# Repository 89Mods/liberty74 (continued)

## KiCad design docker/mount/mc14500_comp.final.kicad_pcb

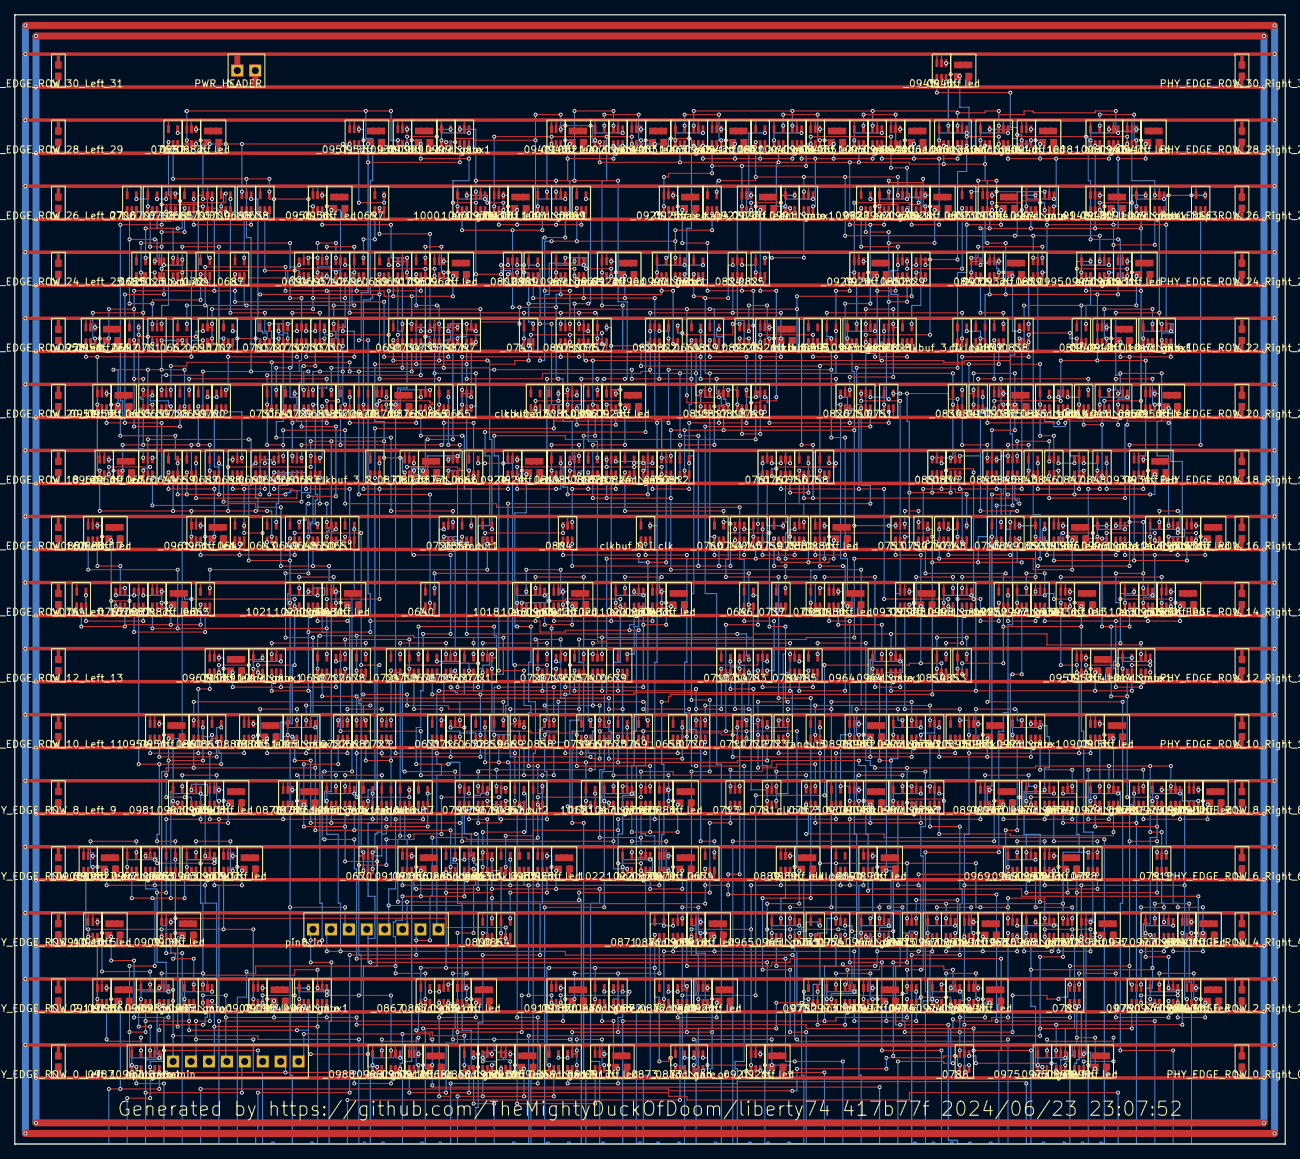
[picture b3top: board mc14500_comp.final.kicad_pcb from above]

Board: 2 copper layers, 180.0 x 160.0 mm, 592 parts (0 on the bottom side), 481 nets.

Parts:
PHY_EDGE_ROW_0_Left_1, PHY_EDGE_ROW_0_Right_0, PHY_EDGE_ROW_2_Left_3, PHY_EDGE_ROW_2_Right_2, PHY_EDGE_ROW_4_Left_5, PHY_EDGE_ROW_4_Right_4, PHY_EDGE_ROW_6_Left_7, PHY_EDGE_ROW_6_Right_6, PHY_EDGE_ROW_8_Left_9, PHY_EDGE_ROW_8_Right_8, PHY_EDGE_ROW_10_Left_11, PHY_EDGE_ROW_10_Right_10, PHY_EDGE_ROW_12_Left_13, PHY_EDGE_ROW_12_Right_12, PHY_EDGE_ROW_14_Left_15, PHY_EDGE_ROW_14_Right_14, PHY_EDGE_ROW_16_Left_17, PHY_EDGE_ROW_16_Right_16, PHY_EDGE_ROW_18_Left_19, PHY_EDGE_ROW_18_Right_18, PHY_EDGE_ROW_20_Left_21, PHY_EDGE_ROW_20_Right_20, PHY_EDGE_ROW_22_Left_23, PHY_EDGE_ROW_22_Right_22, PHY_EDGE_ROW_24_Left_25, PHY_EDGE_ROW_24_Right_24, PHY_EDGE_ROW_26_Left_27, PHY_EDGE_ROW_26_Right_26, PHY_EDGE_ROW_28_Left_29, PHY_EDGE_ROW_28_Right_28, PHY_EDGE_ROW_30_Left_31, PHY_EDGE_ROW_30_Right_30: PWR_CAP; PWR_CAP_N
PWR_HEADER: PWR_HEADER; PWR_HEADER_N
_0635_, _0636_, _0660_, _0711_, _0742_: OR3_74LVC1G332; OR3_74LVC1G332_N
_0638_, _0640_, _0641_, _0642_, _0658_, _0662_, _0671_, _0676_, _0685_, _0692_, _0706_, _0737_, _0764_, _0765_, _0769_, _0801_, _0828_: INV_74LVC1G04; INV_74LVC1G04_N
_0639_, _0683_, _0688_, _0701_, _0712_, _0715_, _0717_, _0719_, _0722_, _0727_, _0729_, _0755_, _0761_, _0774_, _0775_, _0776_, _0777_, _0778_, _0779_, _0780_, _0786_, _0788_, _0789_, _0790_, _0791_, _0792_, _0793_, _0802_, _0829_, _0839_, _0860_, _0863_, _0876__mux, _0877__mux, _0964__mux1, _0965__mux1, _0966__mux1, _0967__mux1, _0968__mux1, _0969__mux1, _0970__mux1, _0971__mux1, _0972__mux1, _0973__mux1, _0974__mux1, _0975__mux1, _0976__mux1, _0977__mux1, _0978__mux1, _0979__mux1, _0980__mux1, _0981__mux1, _0982__mux1, _0983__mux1, _0984__mux1, _0985__mux1, _0986__mux1, _0987__mux1, _0988__mux1, _0989__mux1, _0990__mux1, _0991__mux1, _0992__mux1, _0993__mux1, _0994__mux1, _0995__mux1, _0996__mux1, _0997__mux1, _0998__mux1, _0999__mux1, _1000__mux1, _1001__mux1, _1002__mux1, _1003__mux1, _1004__mux1, _1005__mux1, _1006__mux1, _1007__mux1, _1008__mux1, _1009__mux1, _1010__mux1, _1011__mux1, _1012__mux1, _1013__mux1, _1014__mux1, _1015__mux1, _1016__mux1, _1017__mux1, _1018__mux1, _1019__mux1, _1020__mux1, _1021__mux1, _1022__mux1, _1023__mux1, _1023__mux2: MUX2_74LVC1G157; MUX2_74LVC1G157_N
_0643_, _0659_, _0687_, _0699_, _0704_, _0709_, _0710_, _0718_, _0720_, _0756_, _0758_, _0806_, _0809_, _0861_, _0864_: OR2_74LVC1G32; OR2_74LVC1G32_N
_0644_, _0648_, _0649_, _0682_, _0686_, _0690_, _0702_, _0703_, _0728_, _0731_, _0745_, _0757_, _0760_, _0822_, _0837_: NAND2_74LVC1G00; NAND2_74LVC1G00_N
_0645_, _0667_, _0669_, _0693_, _0700_, _0705_, _0713_, _0726_, _0730_, _0735_, _0740_, _0747_, _0749_, _0750_, _0752_, _0753_, _0754_, _0762_, _0784_, _0794_, _0797_, _0799_, _0803_, _0804_, _0810_, _0815_, _0817_, _0824_, _0826_, _0832_, _0836_, _0840_, _0849_, _0851_, _0858_: AND3_74LVC1G11; AND3_74LVC1G11_N
_0646_, _0651_, _0664_, _0672_, _0673_, _0675_, _0677_, _0678_, _0679_, _0680_, _0681_, _0697_, _0707_, _0724_, _0736_, _0738_, _0743_, _0746_, _0748_, _0751_, _0759_, _0763_, _0771_, _0782_, _0785_, _0814_, _0834_, _0843_, _0844_, _0848_, _0853_, _0856_, _0859_, _0862_, _0866__and_gate, _0867__and_gate, _0868__and_gate, _0869__and_gate, _0870__and_gate, _0871__and_gate, _0872__and_gate, _0873__and_gate, _0874__and_gate, _0875__and_gate, _0964__and_gate, _0965__and_gate, _0966__and_gate, _0967__and_gate, _0968__and_gate, _0969__and_gate, _0970__and_gate, _0971__and_gate, _0972__and_gate, _0973__and_gate, _0974__and_gate, _0975__and_gate, _0976__and_gate, _0977__and_gate, _0978__and_gate, _0979__and_gate, _0980__and_gate, _0981__and_gate, _0982__and_gate, _0983__and_gate, _0984__and_gate, _0985__and_gate, _0986__and_gate, _0987__and_gate, _0988__and_gate, _0989__and_gate, _0990__and_gate, _0991__and_gate, _0992__and_gate, _0993__and_gate, _0994__and_gate, _0995__and_gate, _0996__and_gate, _0997__and_gate, _0998__and_gate, _0999__and_gate, _1000__and_gate, _1001__and_gate, _1002__and_gate, _1003__and_gate, _1004__and_gate, _1005__and_gate, _1006__and_gate, _1007__and_gate, _1008__and_gate, _1009__and_gate, _1010__and_gate, _1011__and_gate, _1012__and_gate, _1013__and_gate, _1014__and_gate, _1015__and_gate, _1016__and_gate, _1017__and_gate, _1018__and_gate, _1019__and_gate, _1020__and_gate, _1021__and_gate, _1022__and_gate: AND2_74LVC1G08; AND2_74LVC1G08_N
_0650_, _0694_, _0695_, _0708_, _0823_, _0845_: NOR3_74LVC1G27; NOR3_74LVC1G27_N
_0661_, _0691_, _0698_, _0714_, _0732_, _0733_, _0734_, _0744_, _0766_, _0767_, _0773_, _0783_, _0811_, _0813_, _0821_, _0830_, _0838_, _0841_, _0846_, _0847_, _0866__and_or, _0867__and_or, _0868__and_or, _0869__and_or, _0870__and_or, _0871__and_or, _0872__and_or, _0873__and_or, _0874__and_or, _0875__and_or: AO21_74LVC1G0832; AO21_74LVC1G0832_N
_0663_, _0666_, _0674_, _0684_, _0689_, _0739_, _0800_, _0812_, _0819_, _0820_, _0857_, _0865_: NOR2_74LVC1G02; NOR2_74LVC1G02_N
_0665_, _0668_, _0670_, _0716_, _0721_, _0723_, _0725_, _0770_, _0772_, _0781_, _0796_, _0798_, _0807_, _0842_: NAND3_74LVC1G10; NAND3_74LVC1G10_N
_0696_, _0805_, _0816_, _0818_, _0825_, _0827_, _0833_, _0835_, _0850_, _0852_, _0854_: XOR2_74LVC1G86; XOR2_74LVC1G86_N
_0876__dff, _0877__dff, _0878__dff, _0879__dff, _0880__dff, _0881__dff, _0882__dff, _0883__dff, _0884__dff, _0885__dff, _0886__dff, _0887__dff, _0888__dff, _0889__dff, _0890__dff, _0891__dff, _0892__dff, _0893__dff, _0894__dff, _0895__dff, _0896__dff, _0897__dff, _0898__dff, _0899__dff, _0900__dff, _0901__dff, _0902__dff, _0903__dff, _0904__dff, _0905__dff, _0906__dff, _0907__dff, _0908__dff, _0909__dff, _0910__dff, _0911__dff, _0912__dff, _0913__dff, _0914__dff, _0915__dff, _0916__dff, _0917__dff, _0918__dff, _0919__dff, _0920__dff, _0921__dff, _0922__dff, _0923__dff, _0924__dff, _0925__dff, _0926__dff, _0927__dff, _0928__dff, _0929__dff, _0930__dff, _0931__dff, _0932__dff, _0933__dff, _0934__dff, _0935__dff, _0936__dff, _0937__dff, _0938__dff, _0939__dff, _0940__dff, _0941__dff, _0942__dff, _0943__dff, _0944__dff, _0945__dff, _0946__dff, _0947__dff, _0948__dff, _0949__dff, _0950__dff, _0951__dff, _0952__dff, _0953__dff, _0954__dff, _0955__dff, _0956__dff, _0957__dff, _0958__dff, _0959__dff, _0960__dff, _0961__dff, _0962__dff, _0963__dff: DFF_74LVC1G175; DFF_74LVC1G175_N
_0876__led, _0877__led, _0878__led, _0879__led, _0880__led, _0881__led, _0882__led, _0883__led, _0884__led, _0885__led, _0886__led, _0887__led, _0888__led, _0889__led, _0890__led, _0891__led, _0892__led, _0893__led, _0894__led, _0895__led, _0896__led, _0897__led, _0898__led, _0899__led, _0900__led, _0901__led, _0902__led, _0903__led, _0904__led, _0905__led, _0906__led, _0907__led, _0908__led, _0909__led, _0910__led, _0911__led, _0912__led, _0913__led, _0914__led, _0915__led, _0916__led, _0917__led, _0918__led, _0919__led, _0920__led, _0921__led, _0922__led, _0923__led, _0924__led, _0925__led, _0926__led, _0927__led, _0928__led, _0929__led, _0930__led, _0931__led, _0932__led, _0933__led, _0934__led, _0935__led, _0936__led, _0937__led, _0938__led, _0939__led, _0940__led, _0941__led, _0942__led, _0943__led, _0944__led, _0945__led, _0946__led, _0947__led, _0948__led, _0949__led, _0950__led, _0951__led, _0952__led, _0953__led, _0954__led, _0955__led, _0956__led, _0957__led, _0958__led, _0959__led, _0960__led, _0961__led, _0962__led, _0963__led: Led_Res_0603; Led_Res_0603_N
clkbuf_0_i_clk, clkbuf_3_0__f_i_clk, clkbuf_3_1__f_i_clk, clkbuf_3_2__f_i_clk, clkbuf_3_3__f_i_clk, clkbuf_3_4__f_i_clk, clkbuf_3_5__f_i_clk, clkbuf_3_6__f_i_clk, clkbuf_3_7__f_i_clk: BUF_74LVC1G125; BUF_74LVC1G125_N
clkload0, clkload1, clkload2, clkload3, clkload4, clkload5, clkload6: BUF_74LVC1G125; BUF_74LVC1G125_N
fanout1, fanout2, fanout5, fanout6, fanout7: BUF_74LVC1G125; BUF_74LVC1G125_N
max_cap3, max_cap4: BUF_74LVC1G125; BUF_74LVC1G125_N
pin8_io, pin8_sramin: PININ_8; PININ_8_N

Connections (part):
DATA_OUT: _0860_.1 (I1), _0863_.1 (I1), _0866__and_gate.2 (A), _0957__dff.4 (Q), _0957__led.1 (I), _0981__mux1.1 (I1), _0999__mux1.1 (I1), _1015__mux1.3 (I0), _1016__mux1.3 (I0), _1017__mux1.1 (I1), _1018__mux1.1 (I1), _1019__mux1.1 (I1), _1020__mux1.1 (I1), _1021__mux1.1 (I1), _1022__mux1.1 (I1)
FLAG_O: _0646_.4 (Y), _0772_.1 (A)
GND: PHY_EDGE_ROW_0_Left_1.1 (GND), PHY_EDGE_ROW_0_Right_0.1 (GND), PHY_EDGE_ROW_2_Left_3.1 (GND), PHY_EDGE_ROW_2_Right_2.1 (GND), PHY_EDGE_ROW_4_Left_5.1 (GND), PHY_EDGE_ROW_4_Right_4.1 (GND), PHY_EDGE_ROW_6_Left_7.1 (GND), PHY_EDGE_ROW_6_Right_6.1 (GND), PHY_EDGE_ROW_8_Left_9.1 (GND), PHY_EDGE_ROW_8_Right_8.1 (GND), PHY_EDGE_ROW_10_Left_11.1 (GND), PHY_EDGE_ROW_10_Right_10.1 (GND), PHY_EDGE_ROW_12_Left_13.1 (GND), PHY_EDGE_ROW_12_Right_12.1 (GND), PHY_EDGE_ROW_14_Left_15.1 (GND), PHY_EDGE_ROW_14_Right_14.1 (GND), PHY_EDGE_ROW_16_Left_17.1 (GND), PHY_EDGE_ROW_16_Right_16.1 (GND), PHY_EDGE_ROW_18_Left_19.1 (GND), PHY_EDGE_ROW_18_Right_18.1 (GND), PHY_EDGE_ROW_20_Left_21.1 (GND), PHY_EDGE_ROW_20_Right_20.1 (GND), PHY_EDGE_ROW_22_Left_23.1 (GND), PHY_EDGE_ROW_22_Right_22.1 (GND), PHY_EDGE_ROW_24_Left_25.1 (GND), PHY_EDGE_ROW_24_Right_24.1 (GND), PHY_EDGE_ROW_26_Left_27.1 (GND), PHY_EDGE_ROW_26_Right_26.1 (GND), PHY_EDGE_ROW_28_Left_29.1 (GND), PHY_EDGE_ROW_28_Right_28.1 (GND), PHY_EDGE_ROW_30_Left_31.1 (GND), PHY_EDGE_ROW_30_Right_30.1 (GND), PWR_HEADER.2 (GND), _0635_.2 (GND), _0636_.2 (GND), _0638_.1 (GND), _0638_.3 (GND), _0639_.2 (GND), _0640_.1 (GND), _0640_.3 (GND), _0641_.1 (GND), _0641_.3 (GND), _0642_.1 (GND), _0642_.3 (GND), _0643_.3 (GND), _0644_.3 (GND), _0645_.2 (GND), _0646_.3 (GND), _0648_.3 (GND), _0649_.3 (GND), _0650_.2 (GND), _0651_.3 (GND), _0658_.1 (GND), _0658_.3 (GND), _0659_.3 (GND), _0660_.2 (GND), _0661_.2 (GND), _0662_.1 (GND), _0662_.3 (GND), _0663_.3 (GND), _0664_.3 (GND), _0665_.2 (GND), _0666_.3 (GND), _0667_.2 (GND), _0668_.2 (GND), _0669_.2 (GND), _0670_.2 (GND), _0671_.1 (GND), _0671_.3 (GND), _0672_.3 (GND), _0673_.3 (GND), _0674_.3 (GND), _0675_.3 (GND), _0676_.1 (GND), _0676_.3 (GND), _0677_.3 (GND), _0678_.3 (GND), _0679_.3 (GND), _0680_.3 (GND), _0681_.3 (GND), _0682_.3 (GND), _0683_.2 (GND), _0684_.3 (GND), _0685_.1 (GND), _0685_.3 (GND), _0686_.3 (GND)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
PC[0]: _0752_.6 (C), _0801_.2 (A), _0804_.1 (A), _0922__dff.4 (Q), _0922__led.1 (I), _0989__mux1.3 (I0)
PC[1]: _0752_.3 (B), _0805_.2 (A), _0811_.1 (A), _0923__dff.4 (Q), _0923__led.1 (I)
PC[2]: _0752_.1 (A), _0811_.6 (C), _0874__and_gate.2 (A), _0924__dff.4 (Q), _0924__led.1 (I)
PC[3]: _0749_.6 (C), _0816_.2 (A), _0817_.1 (A), _0824_.3 (B), _0925__dff.4 (Q), _0925__led.1 (I)
PC[4]: _0749_.3 (B), _0818_.2 (A), _0821_.6 (C), _0824_.1 (A), _0926__dff.4 (Q), _0926__led.1 (I)
PC[5]: _0749_.1 (A), _0825_.2 (A), _0927__dff.4 (Q), _0927__led.1 (I)
PC[6]: _0750_.6 (C), _0827_.2 (A), _0830_.1 (A), _0832_.3 (B), _0928__dff.4 (Q), _0928__led.1 (I)
PC[7]: _0750_.3 (B), _0828_.2 (A), _0832_.1 (A), _0929__dff.4 (Q), _0929__led.1 (I), _0993__mux1.3 (I0)
PC[8]: _0750_.1 (A), _0833_.2 (A), _0930__dff.4 (Q), _0930__led.1 (I)
PC[9]: _0746_.1 (B), _0835_.2 (A), _0838_.1 (A), _0931__dff.4 (Q), _0931__led.1 (I)
PC[10]: _0746_.2 (A), _0838_.6 (C), _0932__dff.4 (Q), _0932__led.1 (I)
PC[11]: _0747_.6 (C), _0841_.6 (C), _0842_.1 (A), _0849_.3 (B), _0933__dff.4 (Q), _0933__led.1 (I)
PC[12]: _0747_.3 (B), _0845_.1 (A), _0847_.1 (A), _0849_.1 (A), _0934__dff.4 (Q), _0934__led.1 (I)
PC[13]: _0747_.1 (A), _0850_.2 (A), _0935__dff.4 (Q), _0935__led.1 (I)
PC[14]: _0754_.1 (A), _0852_.2 (A), _0853_.2 (A), _0936__dff.4 (Q), _0936__led.1 (I)
PC[15]: _0753_.1 (A), _0854_.2 (A), _0937__dff.4 (Q), _0937__led.1 (I)
PC[16]: _0745_.2 (A), _0755_.3 (I0), _0759_.2 (A), _0881__dff.4 (Q), _0881__led.1 (I)
RR: _0689_.2 (A), _0696_.2 (A), _0701_.6 (S), _0704_.1 (B), _0706_.2 (A), _0730_.1 (A), _0734_.6 (C), _0962__dff.4 (Q), _0962__led.1 (I), _1023__mux1.6 (S)
SCLK: _0715_.1 (I1), _0879__dff.4 (Q), _0879__led.1 (I), _1022__mux1.3 (I0)
SDO: _0722_.1 (I1), _0878__dff.4 (Q), _0878__led.1 (I), _1016__mux1.1 (I1)
VDD: PHY_EDGE_ROW_0_Left_1.2 (VDD), PHY_EDGE_ROW_0_Right_0.2 (VDD), PHY_EDGE_ROW_2_Left_3.2 (VDD), PHY_EDGE_ROW_2_Right_2.2 (VDD), PHY_EDGE_ROW_4_Left_5.2 (VDD), PHY_EDGE_ROW_4_Right_4.2 (VDD), PHY_EDGE_ROW_6_Left_7.2 (VDD), PHY_EDGE_ROW_6_Right_6.2 (VDD), PHY_EDGE_ROW_8_Left_9.2 (VDD), PHY_EDGE_ROW_8_Right_8.2 (VDD), PHY_EDGE_ROW_10_Left_11.2 (VDD), PHY_EDGE_ROW_10_Right_10.2 (VDD), PHY_EDGE_ROW_12_Left_13.2 (VDD), PHY_EDGE_ROW_12_Right_12.2 (VDD), PHY_EDGE_ROW_14_Left_15.2 (VDD), PHY_EDGE_ROW_14_Right_14.2 (VDD), PHY_EDGE_ROW_16_Left_17.2 (VDD), PHY_EDGE_ROW_16_Right_16.2 (VDD), PHY_EDGE_ROW_18_Left_19.2 (VDD), PHY_EDGE_ROW_18_Right_18.2 (VDD), PHY_EDGE_ROW_20_Left_21.2 (VDD), PHY_EDGE_ROW_20_Right_20.2 (VDD), PHY_EDGE_ROW_22_Left_23.2 (VDD), PHY_EDGE_ROW_22_Right_22.2 (VDD), PHY_EDGE_ROW_24_Left_25.2 (VDD), PHY_EDGE_ROW_24_Right_24.2 (VDD), PHY_EDGE_ROW_26_Left_27.2 (VDD), PHY_EDGE_ROW_26_Right_26.2 (VDD), PHY_EDGE_ROW_28_Left_29.2 (VDD), PHY_EDGE_ROW_28_Right_28.2 (VDD), PHY_EDGE_ROW_30_Left_31.2 (VDD), PHY_EDGE_ROW_30_Right_30.2 (VDD), PWR_HEADER.1 (VDD), _0635_.5 (VDD), _0636_.5 (VDD), _0638_.6 (VDD), _0639_.5 (VDD), _0640_.6 (VDD), _0641_.6 (VDD), _0642_.6 (VDD), _0643_.6 (VDD), _0644_.6 (VDD), _0645_.5 (VDD), _0646_.6 (VDD), _0648_.6 (VDD), _0649_.6 (VDD), _0650_.5 (VDD), _0651_.6 (VDD), _0658_.6 (VDD), _0659_.6 (VDD), _0660_.5 (VDD), _0661_.5 (VDD), _0662_.6 (VDD), _0663_.6 (VDD), _0664_.6 (VDD), _0665_.5 (VDD), _0666_.6 (VDD), _0667_.5 (VDD), _0668_.5 (VDD), _0669_.5 (VDD), _0670_.5 (VDD), _0671_.6 (VDD), _0672_.6 (VDD), _0673_.6 (VDD), _0674_.6 (VDD), _0675_.6 (VDD), _0676_.6 (VDD), _0677_.6 (VDD), _0678_.6 (VDD), _0679_.6 (VDD), _0680_.6 (VDD), _0681_.6 (VDD), _0682_.6 (VDD), _0683_.5 (VDD), _0684_.6 (VDD), _0685_.6 (VDD), _0686_.6 (VDD), _0687_.6 (VDD), _0688_.5 (VDD), _0689_.6 (VDD), _0690_.6 (VDD), _0691_.5 (VDD), _0692_.6 (VDD), _0693_.5 (VDD), _0694_.5 (VDD), _0695_.5 (VDD)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
X1: _0638_.2 (A), _0643_.2 (A), _0644_.2 (A), _0650_.1 (A), _0660_.1 (A), _0664_.2 (A), _0683_.6 (S), _0688_.6 (S), _0693_.1 (A), _0694_.1 (A), _0698_.6 (C), _0705_.1 (A), _0708_.1 (A), _0744_.1 (A), _0760_.2 (A), _0797_.1 (A), _0804_.3 (B), _0815_.1 (A), _0821_.1 (A), _0876__dff.1 (CLK), _0877__dff.1 (CLK), _0882__dff.4 (Q), _0882__led.1 (I), _0957__dff.1 (CLK), _0958__dff.1 (CLK), _0959__dff.1 (CLK), _0960__dff.1 (CLK), _0961__dff.1 (CLK), _0962__dff.1 (CLK), _1023__mux2.6 (S)
_0000_: _0736_.4 (Y), _0962__dff.3 (D)
_0001_: _0697_.4 (Y), _0957__dff.3 (D)
_0002_: _0691_.4 (Y), _0956__dff.3 (D)
_0003_: _0883__dff.3 (D), _1020__and_gate.4 (Y)
_0004_: _0884__dff.3 (D), _1021__and_gate.4 (Y)
_0005_: _0885__dff.3 (D), _1017__and_gate.4 (Y)
_0006_: _0886__dff.3 (D), _1015__and_gate.4 (Y)
_0007_: _0913__dff.3 (D), _1018__and_gate.4 (Y)
_0008_: _0963__dff.3 (D), _1019__and_gate.4 (Y)
_0009_: _0879__dff.3 (D), _1022__and_gate.4 (Y)
_0010_: _0878__dff.3 (D), _1016__and_gate.4 (Y)
_0011_: _0638_.4 (Y), _0639_.6 (S), _0699_.2 (A), _0729_.6 (S), _0763_.2 (A), _0956__dff.1 (CLK)
_0012_: _0880__dff.3 (D), _0964__and_gate.4 (Y)
_0013_: _0762_.4 (Y), _0881__dff.3 (D)
_0014_: _0763_.4 (Y), _0882__dff.3 (D)
_0015_: _0766_.4 (Y), _0887__dff.3 (D)
_0016_: _0767_.4 (Y), _0888__dff.3 (D)
_0017_: _0889__dff.3 (D), _0965__and_gate.4 (Y)
_0018_: _0890__dff.3 (D), _0966__and_gate.4 (Y)
_0019_: _0891__dff.3 (D), _0967__and_gate.4 (Y)
_0020_: _0892__dff.3 (D), _0968__and_gate.4 (Y)
_0021_: _0893__dff.3 (D), _0969__and_gate.4 (Y)
_0022_: _0894__dff.3 (D), _0970__and_gate.4 (Y)
_0023_: _0895__dff.3 (D), _0971__and_gate.4 (Y)
_0024_: _0896__dff.3 (D), _0972__and_gate.4 (Y)
_0025_: _0897__dff.3 (D), _0973__and_gate.4 (Y)
_0026_: _0898__dff.3 (D), _0974__and_gate.4 (Y)
_0027_: _0899__dff.3 (D), _0975__and_gate.4 (Y)
_0028_: _0900__dff.3 (D), _0976__and_gate.4 (Y)
_0029_: _0901__dff.3 (D), _0977__and_gate.4 (Y)
_0030_: _0902__dff.3 (D), _0978__and_gate.4 (Y)
_0031_: _0903__dff.3 (D), _0979__and_gate.4 (Y)
_0032_: _0904__dff.3 (D), _0980__and_gate.4 (Y)
_0033_: _0905__dff.3 (D), _0981__and_gate.4 (Y)
_0034_: _0906__dff.3 (D), _0982__and_gate.4 (Y)
_0035_: _0907__dff.3 (D), _0983__and_gate.4 (Y)
_0036_: _0908__dff.3 (D), _0984__and_gate.4 (Y)
_0037_: _0909__dff.3 (D), _0985__and_gate.4 (Y)
_0038_: _0910__dff.3 (D), _0986__and_gate.4 (Y)
_0039_: _0911__dff.3 (D), _0987__and_gate.4 (Y)
_0040_: _0912__dff.3 (D), _0988__and_gate.4 (Y)
_0041_: _0866__and_or.4 (Y), _0914__dff.3 (D)
_0042_: _0867__and_or.4 (Y), _0915__dff.3 (D)
_0043_: _0868__and_or.4 (Y), _0916__dff.3 (D)
_0044_: _0869__and_or.4 (Y), _0917__dff.3 (D)
_0045_: _0870__and_or.4 (Y), _0918__dff.3 (D)
_0046_: _0871__and_or.4 (Y), _0919__dff.3 (D)
_0047_: _0872__and_or.4 (Y), _0920__dff.3 (D)
_0048_: _0873__and_or.4 (Y), _0921__dff.3 (D)
_0049_: _0922__dff.3 (D), _0989__and_gate.4 (Y)
_0050_: _0810_.4 (Y), _0923__dff.3 (D)
_0051_: _0814_.4 (Y), _0924__dff.3 (D)
_0052_: _0925__dff.3 (D), _0990__and_gate.4 (Y)
_0053_: _0823_.4 (Y), _0926__dff.3 (D)
_0054_: _0927__dff.3 (D), _0991__and_gate.4 (Y)
_0055_: _0928__dff.3 (D), _0992__and_gate.4 (Y)
_0056_: _0929__dff.3 (D), _0993__and_gate.4 (Y)
_0057_: _0930__dff.3 (D), _0994__and_gate.4 (Y)
_0058_: _0931__dff.3 (D), _0995__and_gate.4 (Y)
_0059_: _0840_.4 (Y), _0932__dff.3 (D)
_0060_: _0844_.4 (Y), _0933__dff.3 (D)
_0061_: _0848_.4 (Y), _0934__dff.3 (D)
_0062_: _0935__dff.3 (D), _0996__and_gate.4 (Y)
_0063_: _0936__dff.3 (D), _0997__and_gate.4 (Y)
_0064_: _0937__dff.3 (D), _0998__and_gate.4 (Y)
_0065_: _0938__dff.3 (D), _0999__and_gate.4 (Y)
_0066_: _0939__dff.3 (D), _1000__and_gate.4 (Y)
_0067_: _0940__dff.3 (D), _1001__and_gate.4 (Y)
_0068_: _0941__dff.3 (D), _1002__and_gate.4 (Y)
_0069_: _0942__dff.3 (D), _1003__and_gate.4 (Y)
_0070_: _0943__dff.3 (D), _1004__and_gate.4 (Y)
_0071_: _0944__dff.3 (D), _1005__and_gate.4 (Y)
_0072_: _0945__dff.3 (D), _1006__and_gate.4 (Y)
_0073_: _0946__dff.3 (D), _1007__and_gate.4 (Y)
_0074_: _0947__dff.3 (D), _1008__and_gate.4 (Y)
_0075_: _0948__dff.3 (D), _1009__and_gate.4 (Y)
_0076_: _0949__dff.3 (D), _1010__and_gate.4 (Y)
_0077_: _0950__dff.3 (D), _1011__and_gate.4 (Y)
_0078_: _0951__dff.3 (D), _1012__and_gate.4 (Y)
_0079_: _0952__dff.3 (D), _1013__and_gate.4 (Y)
_0080_: _0953__dff.3 (D), _1014__and_gate.4 (Y)
_0082_: _0861_.4 (Y), _0954__dff.3 (D)
_0083_: _0864_.4 (Y), _0955__dff.3 (D)
_0085_: _0635_.4 (Y), _0639_.3 (I0)
_0086_: _0636_.4 (Y), _0639_.1 (I1)
_0088_: _0639_.4 (Y), _0640_.2 (A), _0731_.2 (A), _0734_.1 (A)
_0089_: _0640_.4 (Y), _0646_.2 (A), _0783_.1 (A)
_0090_: _0641_.4 (Y), _0645_.1 (A), _0651_.2 (A), _0733_.1 (A)
_0091_: _0642_.4 (Y), _0643_.1 (B), _0660_.3 (B), _0698_.1 (A)
_0092_: _0643_.4 (Y), _0645_.3 (B)
_0093_: _0644_.4 (Y), _0645_.6 (C), _0659_.1 (B), _0700_.1 (A)
_0094_: _0645_.4 (Y), _0646_.1 (B), _0731_.1 (B), _0734_.3 (B), _0783_.3 (B)
_0096_: _0648_.4 (Y), _0650_.3 (B), _0729_.1 (I1)
_0097_: _0649_.4 (Y), _0650_.6 (C), _0683_.3 (I0)
_0098_: _0650_.4 (Y), _0651_.1 (B)
_0105_: _0658_.4 (Y), _0667_.3 (B), _0711_.6 (C)
_0106_: _0659_.4 (Y), _0661_.1 (A)
_0107_: _0660_.4 (Y), _0661_.3 (B)
_0108_: _0661_.4 (Y), _0666_.2 (A), _0857_.1 (B), _0865_.2 (A)
_0109_: _0662_.4 (Y), _0665_.1 (A), _0687_.2 (A), _0693_.3 (B), _0704_.2 (A), _0797_.3 (B)
_0110_: _0663_.4 (Y), _0804_.6 (C), fanout1.2 (A)
_0111_: _0664_.4 (Y), _0665_.6 (C), _0784_.3 (B), _0803_.1 (A), _0807_.1 (A), _0817_.3 (B), _0826_.1 (A), _0989__mux1.6 (S)
_0112_: _0665_.4 (Y), _0666_.1 (B)
_0113_: _0666_.4 (Y), _0667_.6 (C), _0669_.6 (C), _0740_.1 (A), _0794_.1 (A), _0796_.1 (A), _0858_.6 (C)
_0114_: _0667_.4 (Y), _0668_.6 (C), _0673_.2 (A), _0679_.2 (A), _0680_.2 (A)
_0115_: _0668_.4 (Y), _1015__mux1.6 (S)
_0117_: _0669_.4 (Y), _0670_.6 (C), _0675_.2 (A), _0678_.2 (A), _0681_.2 (A)
_0118_: _0670_.4 (Y), _1016__mux1.6 (S)
_0120_: _0671_.4 (Y), _0672_.1 (B), _0716_.3 (B), _0718_.2 (A)
_0121_: _0672_.4 (Y), _0673_.1 (B), _0681_.1 (B), _0772_.3 (B), _0794_.3 (B), _0859_.2 (A)
_0122_: _0673_.4 (Y), _1017__mux1.6 (S)
_0124_: _0674_.4 (Y), _0675_.1 (B), _0679_.1 (B), _0710_.1 (B), _0740_.3 (B), _0770_.6 (C)
_0125_: _0675_.4 (Y), _1018__mux1.6 (S)
_0127_: _0676_.4 (Y), _0677_.2 (A), _0721_.1 (A)
_0128_: _0677_.4 (Y), _0678_.1 (B), _0680_.1 (B), _0796_.3 (B), _0862_.2 (A)
_0129_: _0678_.4 (Y), _1019__mux1.6 (S)
_0131_: _0679_.4 (Y), _1020__mux1.6 (S)
_0133_: _0680_.4 (Y), _1021__mux1.6 (S)
_0135_: _0681_.4 (Y), _1022__mux1.6 (S)
_0137_: _0682_.4 (Y), _0683_.1 (I1)
_0138_: _0683_.4 (Y), _0684_.1 (B)
_0139_: _0684_.4 (Y), _0691_.1 (A), _0743_.2 (A), _0757_.2 (A), _0798_.6 (C), _0803_.3 (B), _0807_.3 (B)
_0140_: _0685_.4 (Y), _0686_.1 (B), _0708_.3 (B), _1023__mux1.1 (I1)
_0141_: _0686_.4 (Y), _0688_.3 (I0)
_0142_: _0687_.4 (Y), _0688_.1 (I1)
_0143_: _0688_.4 (Y), _0689_.1 (B), _0703_.2 (A), _0865_.1 (B)
_0144_: _0689_.4 (Y), _0691_.3 (B)
_0145_: _0690_.4 (Y), _0691_.6 (C)
_0146_: _0692_.4 (Y), _0693_.6 (C), _0701_.1 (I1)
_0147_: _0693_.4 (Y), _0695_.3 (B), _0742_.3 (B)
_0148_: _0694_.4 (Y), _0695_.6 (C), _0742_.6 (C)
_0149_: _0695_.4 (Y), _0696_.1 (B), _0730_.6 (C)
_0150_: _0696_.4 (Y), _0697_.1 (B)
_0151_: _0698_.4 (Y), _0700_.3 (B)
_0152_: _0699_.4 (Y), _0700_.6 (C)
_0153_: _0700_.4 (Y), _0702_.2 (A), _0732_.1 (A)
_0155_: _0701_.4 (Y), _1023__mux2.1 (I1)
_0156_: _0702_.1 (B), _1023__mux2.4 (Y)
_0157_: _0702_.4 (Y), _0703_.1 (B)
_0158_: _0703_.4 (Y), _0727_.3 (I0)
_0159_: _0704_.4 (Y), _0705_.6 (C)
_0160_: _0705_.4 (Y), _0709_.2 (A)
_0161_: _0706_.4 (Y), _0707_.1 (B)
_0162_: _0707_.4 (Y), _0708_.6 (C)
_0163_: _0708_.4 (Y), _0709_.1 (B)
_0164_: _0709_.4 (Y), _0727_.1 (I1)
_0165_: _0710_.4 (Y), _0714_.1 (A)
_0166_: _0711_.4 (Y), _0714_.3 (B)
_0167_: _0712_.4 (Y), _0713_.6 (C)
_0168_: _0713_.4 (Y), _0714_.6 (C)
_0169_: _0714_.4 (Y), _0726_.3 (B), _0856_.2 (A)
_0170_: _0715_.4 (Y), _0716_.6 (C)
_0171_: _0716_.4 (Y), _0725_.1 (A)
_0172_: _0717_.4 (Y), _0718_.1 (B)
_0173_: _0718_.4 (Y), _0721_.3 (B)
_0174_: _0719_.4 (Y), _0720_.1 (B)
_0175_: _0720_.4 (Y), _0721_.6 (C)
_0176_: _0721_.4 (Y), _0725_.3 (B)
_0177_: _0722_.4 (Y), _0723_.6 (C)
_0178_: _0723_.4 (Y), _0724_.1 (B)
_0179_: _0724_.4 (Y), _0725_.6 (C)
_0180_: _0725_.4 (Y), _0726_.6 (C), _0856_.1 (B)
_0181_: _0726_.4 (Y), _0727_.6 (S)
_0182_: _0727_.4 (Y), _0733_.3 (B)
_0183_: _0728_.4 (Y), _0729_.3 (I0)
_0184_: _0729_.4 (Y), _0730_.3 (B), _0857_.2 (A)
_0185_: _0730_.4 (Y), _0732_.3 (B)
_0186_: _0731_.4 (Y), _0732_.6 (C)
_0187_: _0732_.4 (Y), _0733_.6 (C)
_0188_: _0733_.4 (Y), _0736_.2 (A)
_0189_: _0734_.4 (Y), _0735_.6 (C)
_0190_: _0735_.4 (Y), _0736_.1 (B)
_0191_: _0737_.4 (Y), _0738_.2 (A), _0759_.1 (B)
_0192_: _0738_.4 (Y), _0964__mux1.3 (I0)
_0193_: _0739_.4 (Y), _0740_.6 (C), _0772_.6 (C), _0781_.6 (C), _0784_.6 (C), _0794_.6 (C), _0796_.6 (C)
_0194_: _0740_.4 (Y), _0964__mux1.6 (S), _0999__mux1.6 (S), _1000__mux1.6 (S), _1001__mux1.6 (S), _1002__mux1.6 (S), _1013__mux1.6 (S), _1014__mux1.6 (S), max_cap3.2 (A)
_0197_: _0742_.4 (Y), _0743_.1 (B), _0757_.1 (B), _0803_.6 (C), _0807_.6 (C)
_0198_: _0743_.4 (Y), _0756_.2 (A), _0802_.6 (S), _0812_.1 (B), _0819_.2 (A), _0829_.6 (S), _0845_.3 (B)
_0199_: _0744_.4 (Y), _0745_.1 (B)
_0200_: _0745_.4 (Y), _0755_.1 (I1)
_0201_: _0746_.4 (Y), _0748_.2 (A), _0836_.3 (B), _0842_.3 (B)
_0202_: _0747_.4 (Y), _0748_.1 (B)
_0203_: _0748_.4 (Y), _0754_.3 (B), _0851_.3 (B)
_0204_: _0749_.4 (Y), _0751_.2 (A), _0826_.3 (B)
_0205_: _0750_.4 (Y), _0751_.1 (B)
_0206_: _0751_.4 (Y), _0753_.3 (B), _0834_.2 (A), _0836_.1 (A), _0851_.1 (A)
_0207_: _0752_.4 (Y), _0753_.6 (C), _0812_.2 (A), _0815_.6 (C), _0817_.6 (C), _0826_.6 (C)
_0208_: _0753_.4 (Y), _0754_.6 (C)
_0209_: _0754_.4 (Y), _0755_.6 (S)
_0210_: _0755_.4 (Y), _0756_.1 (B)
_0211_: _0756_.4 (Y), _0762_.3 (B)
_0212_: _0757_.4 (Y), _0758_.1 (B), _0837_.2 (A), _0841_.1 (A)
_0213_: _0758_.4 (Y), _0761_.3 (I0)
_0214_: _0759_.4 (Y), _0761_.1 (I1)
_0215_: _0760_.4 (Y), _0761_.6 (S), _0773_.6 (C), _0874__and_gate.1 (B)
_0216_: _0761_.4 (Y), _0762_.6 (C)
_0217_: _0764_.4 (Y), _0766_.3 (B)
_0218_: _0765_.4 (Y), _0766_.6 (C), _0767_.6 (C), _0800_.2 (A), _0861_.2 (A), _0864_.2 (A)
_0220_: _0769_.4 (Y), _0770_.1 (A), _0858_.1 (A)
_0221_: _0770_.4 (Y), _0780_.6 (S), fanout5.2 (A)
_0222_: _0771_.4 (Y), _0965__mux1.3 (I0)
_0223_: _0772_.4 (Y), _0773_.3 (B)
_0224_: _0773_.4 (Y), _0965__mux1.6 (S), _0966__mux1.6 (S), _0967__mux1.6 (S), _0968__mux1.6 (S), _0969__mux1.6 (S), _0970__mux1.6 (S), _0971__mux1.6 (S), _0972__mux1.6 (S)
_0226_: _0774_.4 (Y), _0966__mux1.3 (I0)
_0228_: _0775_.4 (Y), _0967__mux1.3 (I0)
_0230_: _0776_.4 (Y), _0968__mux1.3 (I0)
_0232_: _0777_.4 (Y), _0969__mux1.3 (I0)
_0234_: _0778_.4 (Y), _0970__mux1.3 (I0)
_0236_: _0779_.4 (Y), _0971__mux1.3 (I0)
_0238_: _0780_.4 (Y), _0972__mux1.3 (I0)
_0240_: _0781_.4 (Y), _0782_.1 (B), _0786_.6 (S), _0788_.6 (S), _0789_.6 (S), _0790_.6 (S), _0791_.6 (S), _0792_.6 (S), _0793_.6 (S)
_0241_: _0782_.4 (Y), _0973__mux1.1 (I1)
_0242_: _0783_.4 (Y), _0785_.2 (A)
_0243_: _0784_.4 (Y), _0785_.1 (B)
_0244_: _0785_.4 (Y), _0973__mux1.6 (S), _0974__mux1.6 (S), _0975__mux1.6 (S), _0976__mux1.6 (S), _0977__mux1.6 (S), _0978__mux1.6 (S), _0979__mux1.6 (S), _0980__mux1.6 (S)
_0246_: _0786_.4 (Y), _0974__mux1.1 (I1)
_0249_: _0788_.4 (Y), _0975__mux1.1 (I1)
_0251_: _0789_.4 (Y), _0976__mux1.1 (I1)
_0253_: _0790_.4 (Y), _0977__mux1.1 (I1)
_0255_: _0791_.4 (Y), _0978__mux1.1 (I1)
_0257_: _0792_.4 (Y), _0979__mux1.1 (I1)
_0259_: _0793_.4 (Y), _0980__mux1.1 (I1)
_0261_: _0794_.4 (Y), _0981__mux1.6 (S), _0982__mux1.6 (S), _0983__mux1.6 (S), _0984__mux1.6 (S), _0985__mux1.6 (S), _0986__mux1.6 (S), _0987__mux1.6 (S), _0988__mux1.6 (S)
_0271_: _0796_.4 (Y), _0799_.3 (B), _0800_.1 (B)
_0272_: _0797_.4 (Y), _0798_.3 (B)
_0273_: _0798_.4 (Y), _0799_.6 (C)
_0274_: _0799_.4 (Y), _0866__and_or.3 (B), _0867__and_or.3 (B), _0868__and_or.3 (B), _0869__and_or.3 (B), _0870__and_or.3 (B), _0871__and_or.3 (B), _0872__and_or.3 (B), _0873__and_or.3 (B)
_0275_: _0800_.4 (Y), _0866__and_gate.1 (B), _0867__and_gate.1 (B), _0868__and_gate.1 (B), _0869__and_gate.1 (B), _0870__and_gate.1 (B), _0871__and_gate.1 (B), _0872__and_gate.1 (B), _0873__and_gate.1 (B)
_0284_: _0801_.4 (Y), _0802_.3 (I0)
_0285_: _0802_.4 (Y), _0989__mux1.1 (I1)
_0287_: _0803_.4 (Y), _0806_.2 (A), _0813_.3 (B), _0830_.6 (C), _0846_.3 (B), _0875__and_gate.1 (B)
_0288_: _0804_.4 (Y), _0805_.1 (B), _0811_.3 (B)
_0289_: _0805_.4 (Y), _0806_.1 (B)
_0290_: _0806_.4 (Y), _0810_.3 (B)
_0291_: _0807_.4 (Y), _0809_.1 (B), _0990__mux1.6 (S), max_cap4.2 (A)
_0293_: _0809_.4 (Y), _0810_.6 (C)
_0294_: _0811_.4 (Y), _0874__and_or.1 (A)
_0295_: _0812_.4 (Y), _0874__and_or.3 (B)
_0297_: _0813_.6 (C), _0874__and_or.4 (Y)
_0298_: _0813_.4 (Y), _0814_.1 (B)
_0299_: _0815_.4 (Y), _0816_.1 (B), _0824_.6 (C), _0834_.1 (B), _0836_.6 (C), _0851_.6 (C)
_0300_: _0816_.4 (Y), _0990__mux1.1 (I1)
_0302_: _0817_.4 (Y), _0818_.1 (B)
_0303_: _0818_.4 (Y), _0819_.1 (B)
_0304_: _0819_.4 (Y), _0823_.1 (A)
_0305_: _0820_.4 (Y), _0823_.3 (B)
_0306_: _0821_.4 (Y), _0822_.1 (B)
_0307_: _0822_.4 (Y), _0823_.6 (C)
_0308_: _0824_.4 (Y), _0825_.1 (B)
_0309_: _0825_.4 (Y), _0991__mux1.1 (I1)
_0311_: _0826_.4 (Y), _0827_.1 (B), _0830_.3 (B), _0832_.6 (C)
_0312_: _0827_.4 (Y), _0992__mux1.1 (I1)
_0314_: _0828_.4 (Y), _0829_.3 (I0)
_0315_: _0829_.4 (Y), _0993__mux1.1 (I1)
_0316_: _0830_.4 (Y), _0993__mux1.6 (S)
_0319_: _0832_.4 (Y), _0833_.1 (B)
_0320_: _0833_.4 (Y), _0994__mux1.1 (I1)
_0322_: _0834_.4 (Y), _0835_.1 (B), _0838_.3 (B), _0842_.6 (C)
_0323_: _0835_.4 (Y), _0995__mux1.1 (I1)
_0325_: _0836_.4 (Y), _0837_.1 (B), _0841_.3 (B), _0849_.6 (C)
_0326_: _0837_.4 (Y), _0840_.3 (B)
_0327_: _0838_.4 (Y), _0839_.1 (I1)
_0328_: _0839_.4 (Y), _0840_.6 (C)
_0329_: _0841_.4 (Y), _0875__and_or.1 (A)
_0330_: _0842_.4 (Y), _0843_.1 (B), _0845_.6 (C)
_0331_: _0843_.4 (Y), _0847_.3 (B), _0875__and_or.3 (B)
_0333_: _0844_.1 (B), _0875__and_or.4 (Y)
_0334_: _0845_.4 (Y), _0846_.6 (C)
_0335_: _0846_.4 (Y), _0847_.6 (C)
_0336_: _0847_.4 (Y), _0848_.1 (B)
_0337_: _0849_.4 (Y), _0850_.1 (B)
_0338_: _0850_.4 (Y), _0996__mux1.1 (I1)
_0340_: _0851_.4 (Y), _0852_.1 (B), _0853_.1 (B)
_0341_: _0852_.4 (Y), _0997__mux1.1 (I1)
_0343_: _0853_.4 (Y), _0854_.1 (B)
_0344_: _0854_.4 (Y), _0998__mux1.1 (I1)
_0363_: _0856_.4 (Y), _0876__mux.1 (I1), _0877__mux.1 (I1)
_0364_: _0857_.4 (Y), _0876__mux.6 (S)
_0365_: _0858_.4 (Y), _0859_.1 (B), _0862_.1 (B)
_0366_: _0859_.4 (Y), _0860_.6 (S)
_0367_: _0860_.4 (Y), _0861_.1 (B)
_0368_: _0862_.4 (Y), _0863_.6 (S)
_0369_: _0863_.4 (Y), _0864_.1 (B)
_0370_: _0865_.4 (Y), _0877__mux.6 (S)
_0866__a_and: _0866__and_gate.4 (Y), _0866__and_or.6 (C)
_0867__a_and: _0867__and_gate.4 (Y), _0867__and_or.6 (C)
_0868__a_and: _0868__and_gate.4 (Y), _0868__and_or.6 (C)
_0869__a_and: _0869__and_gate.4 (Y), _0869__and_or.6 (C)
_0870__a_and: _0870__and_gate.4 (Y), _0870__and_or.6 (C)
_0871__a_and: _0871__and_gate.4 (Y), _0871__and_or.6 (C)
_0872__a_and: _0872__and_gate.4 (Y), _0872__and_or.6 (C)
_0873__a_and: _0873__and_gate.4 (Y), _0873__and_or.6 (C)
_0874__a_and: _0874__and_gate.4 (Y), _0874__and_or.6 (C)
_0875__a_and: _0875__and_gate.4 (Y), _0875__and_or.6 (C)
_0876__d_selected: _0876__dff.3 (D), _0876__mux.4 (Y)
_0877__d_selected: _0877__dff.3 (D), _0877__mux.4 (Y)
_0964__mux1_data: _0964__and_gate.1 (B), _0964__mux1.4 (Y)
_0965__mux1_data: _0965__and_gate.1 (B), _0965__mux1.4 (Y)
_0966__mux1_data: _0966__and_gate.1 (B), _0966__mux1.4 (Y)
_0967__mux1_data: _0967__and_gate.1 (B), _0967__mux1.4 (Y)
_0968__mux1_data: _0968__and_gate.1 (B), _0968__mux1.4 (Y)
_0969__mux1_data: _0969__and_gate.1 (B), _0969__mux1.4 (Y)
_0970__mux1_data: _0970__and_gate.1 (B), _0970__mux1.4 (Y)
_0971__mux1_data: _0971__and_gate.1 (B), _0971__mux1.4 (Y)
_0972__mux1_data: _0972__and_gate.1 (B), _0972__mux1.4 (Y)
_0973__mux1_data: _0973__and_gate.1 (B), _0973__mux1.4 (Y)
_0974__mux1_data: _0974__and_gate.1 (B), _0974__mux1.4 (Y)
_0975__mux1_data: _0975__and_gate.1 (B), _0975__mux1.4 (Y)
_0976__mux1_data: _0976__and_gate.1 (B), _0976__mux1.4 (Y)
_0977__mux1_data: _0977__and_gate.1 (B), _0977__mux1.4 (Y)
_0978__mux1_data: _0978__and_gate.1 (B), _0978__mux1.4 (Y)
_0979__mux1_data: _0979__and_gate.1 (B), _0979__mux1.4 (Y)
_0980__mux1_data: _0980__and_gate.1 (B), _0980__mux1.4 (Y)
_0981__mux1_data: _0981__and_gate.1 (B), _0981__mux1.4 (Y)
_0982__mux1_data: _0982__and_gate.1 (B), _0982__mux1.4 (Y)
_0983__mux1_data: _0983__and_gate.1 (B), _0983__mux1.4 (Y)
_0984__mux1_data: _0984__and_gate.1 (B), _0984__mux1.4 (Y)
_0985__mux1_data: _0985__and_gate.1 (B), _0985__mux1.4 (Y)
_0986__mux1_data: _0986__and_gate.1 (B), _0986__mux1.4 (Y)
_0987__mux1_data: _0987__and_gate.1 (B), _0987__mux1.4 (Y)
_0988__mux1_data: _0988__and_gate.1 (B), _0988__mux1.4 (Y)
_0989__mux1_data: _0989__and_gate.1 (B), _0989__mux1.4 (Y)
_0990__mux1_data: _0990__and_gate.1 (B), _0990__mux1.4 (Y)
_0991__mux1_data: _0991__and_gate.1 (B), _0991__mux1.4 (Y)
_0992__mux1_data: _0992__and_gate.1 (B), _0992__mux1.4 (Y)
_0993__mux1_data: _0993__and_gate.1 (B), _0993__mux1.4 (Y)
_0994__mux1_data: _0994__and_gate.1 (B), _0994__mux1.4 (Y)
_0995__mux1_data: _0995__and_gate.1 (B), _0995__mux1.4 (Y)
_0996__mux1_data: _0996__and_gate.1 (B), _0996__mux1.4 (Y)
_0997__mux1_data: _0997__and_gate.1 (B), _0997__mux1.4 (Y)
_0998__mux1_data: _0998__and_gate.1 (B), _0998__mux1.4 (Y)
_0999__mux1_data: _0999__and_gate.1 (B), _0999__mux1.4 (Y)
_1000__mux1_data: _1000__and_gate.1 (B), _1000__mux1.4 (Y)
_1001__mux1_data: _1001__and_gate.1 (B), _1001__mux1.4 (Y)
_1002__mux1_data: _1002__and_gate.1 (B), _1002__mux1.4 (Y)
_1003__mux1_data: _1003__and_gate.1 (B), _1003__mux1.4 (Y)
_1004__mux1_data: _1004__and_gate.1 (B), _1004__mux1.4 (Y)
_1005__mux1_data: _1005__and_gate.1 (B), _1005__mux1.4 (Y)
_1006__mux1_data: _1006__and_gate.1 (B), _1006__mux1.4 (Y)
_1007__mux1_data: _1007__and_gate.1 (B), _1007__mux1.4 (Y)
_1008__mux1_data: _1008__and_gate.1 (B), _1008__mux1.4 (Y)
_1009__mux1_data: _1009__and_gate.1 (B), _1009__mux1.4 (Y)
_1010__mux1_data: _1010__and_gate.1 (B), _1010__mux1.4 (Y)
_1011__mux1_data: _1011__and_gate.1 (B), _1011__mux1.4 (Y)
_1012__mux1_data: _1012__and_gate.1 (B), _1012__mux1.4 (Y)
_1013__mux1_data: _1013__and_gate.1 (B), _1013__mux1.4 (Y)
_1014__mux1_data: _1014__and_gate.1 (B), _1014__mux1.4 (Y)
_1015__mux1_data: _1015__and_gate.1 (B), _1015__mux1.4 (Y)
_1016__mux1_data: _1016__and_gate.1 (B), _1016__mux1.4 (Y)
_1017__mux1_data: _1017__and_gate.1 (B), _1017__mux1.4 (Y)
_1018__mux1_data: _1018__and_gate.1 (B), _1018__mux1.4 (Y)
_1019__mux1_data: _1019__and_gate.1 (B), _1019__mux1.4 (Y)
_1020__mux1_data: _1020__and_gate.1 (B), _1020__mux1.4 (Y)
_1021__mux1_data: _1021__and_gate.1 (B), _1021__mux1.4 (Y)
_1022__mux1_data: _1022__and_gate.1 (B), _1022__mux1.4 (Y)
_1023__mux1_data: _1023__mux1.4 (Y), _1023__mux2.3 (I0)
clknet_0_i_clk: clkbuf_0_i_clk.4 (Y), clkbuf_3_0__f_i_clk.2 (A), clkbuf_3_1__f_i_clk.2 (A), clkbuf_3_2__f_i_clk.2 (A), clkbuf_3_3__f_i_clk.2 (A), clkbuf_3_4__f_i_clk.2 (A), clkbuf_3_5__f_i_clk.2 (A), clkbuf_3_6__f_i_clk.2 (A), clkbuf_3_7__f_i_clk.2 (A)
clknet_3_0__leaf_i_clk: _0878__dff.1 (CLK), _0886__dff.1 (CLK), _0905__dff.1 (CLK), _0906__dff.1 (CLK), _0907__dff.1 (CLK), _0908__dff.1 (CLK), _0909__dff.1 (CLK), _0910__dff.1 (CLK), _0911__dff.1 (CLK), _0954__dff.1 (CLK), _0963__dff.1 (CLK), clkbuf_3_0__f_i_clk.4 (Y), clkload0.2 (A)
clknet_3_1__leaf_i_clk: _0879__dff.1 (CLK), _0885__dff.1 (CLK), _0912__dff.1 (CLK), _0914__dff.1 (CLK), _0915__dff.1 (CLK), _0916__dff.1 (CLK), _0917__dff.1 (CLK), _0918__dff.1 (CLK), _0955__dff.1 (CLK), clkbuf_3_1__f_i_clk.4 (Y), clkload1.2 (A)
clknet_3_2__leaf_i_clk: _0882__dff.1 (CLK), _0884__dff.1 (CLK), _0887__dff.1 (CLK), _0888__dff.1 (CLK), _0924__dff.1 (CLK), _0938__dff.1 (CLK), clkbuf_3_2__f_i_clk.4 (Y), clkload2.2 (A)
clknet_3_3__leaf_i_clk: _0883__dff.1 (CLK), _0913__dff.1 (CLK), _0922__dff.1 (CLK), _0923__dff.1 (CLK), _0939__dff.1 (CLK), _0940__dff.1 (CLK), _0941__dff.1 (CLK), clkbuf_3_3__f_i_clk.4 (Y), clkload3.2 (A)
clknet_3_4__leaf_i_clk: _0880__dff.1 (CLK), _0889__dff.1 (CLK), _0890__dff.1 (CLK), _0894__dff.1 (CLK), _0896__dff.1 (CLK), _0897__dff.1 (CLK), _0904__dff.1 (CLK), _0919__dff.1 (CLK), _0920__dff.1 (CLK), _0921__dff.1 (CLK), clkbuf_3_4__f_i_clk.4 (Y), clkload4.2 (A)
clknet_3_5__leaf_i_clk: _0891__dff.1 (CLK), _0892__dff.1 (CLK), _0893__dff.1 (CLK), _0895__dff.1 (CLK), _0898__dff.1 (CLK), _0899__dff.1 (CLK), _0900__dff.1 (CLK), _0901__dff.1 (CLK), _0902__dff.1 (CLK), _0903__dff.1 (CLK), _0936__dff.1 (CLK), _0937__dff.1 (CLK), _0952__dff.1 (CLK), _0953__dff.1 (CLK), clkbuf_3_5__f_i_clk.4 (Y)
clknet_3_6__leaf_i_clk: _0881__dff.1 (CLK), _0925__dff.1 (CLK), _0926__dff.1 (CLK), _0927__dff.1 (CLK), _0928__dff.1 (CLK), _0929__dff.1 (CLK), _0942__dff.1 (CLK), _0943__dff.1 (CLK), _0944__dff.1 (CLK), clkbuf_3_6__f_i_clk.4 (Y), clkload5.2 (A)
clknet_3_7__leaf_i_clk: _0930__dff.1 (CLK), _0931__dff.1 (CLK), _0932__dff.1 (CLK), _0933__dff.1 (CLK), _0934__dff.1 (CLK), _0935__dff.1 (CLK), _0945__dff.1 (CLK), _0946__dff.1 (CLK), _0947__dff.1 (CLK), _0948__dff.1 (CLK), _0949__dff.1 (CLK), _0950__dff.1 (CLK), _0951__dff.1 (CLK), clkbuf_3_7__f_i_clk.4 (Y), clkload6.2 (A)
custom_setting: _0737_.2 (A), _0744_.6 (C)
dest[0]: _0802_.1 (I1), _0938__dff.4 (Q), _0938__led.1 (I), _0999__mux1.3 (I0), _1000__mux1.1 (I1)
dest[1]: _0809_.2 (A), _0939__dff.4 (Q), _0939__led.1 (I), _1000__mux1.3 (I0), _1001__mux1.1 (I1)
dest[2]: _0813_.1 (A), _0940__dff.4 (Q), _0940__led.1 (I), _1001__mux1.3 (I0), _1002__mux1.1 (I1)
dest[3]: _0941__dff.4 (Q), _0941__led.1 (I), _0990__mux1.3 (I0), _1002__mux1.3 (I0), _1003__mux1.1 (I1)
dest[4]: _0820_.2 (A), _0942__dff.4 (Q), _0942__led.1 (I), _1003__mux1.3 (I0), _1004__mux1.1 (I1)
dest[5]: _0943__dff.4 (Q), _0943__led.1 (I), _0991__mux1.3 (I0), _1004__mux1.3 (I0), _1005__mux1.1 (I1)
dest[6]: _0944__dff.4 (Q), _0944__led.1 (I), _0992__mux1.3 (I0), _1005__mux1.3 (I0), _1006__mux1.1 (I1)
dest[7]: _0829_.1 (I1), _0945__dff.4 (Q), _0945__led.1 (I), _1006__mux1.3 (I0), _1007__mux1.1 (I1)
dest[8]: _0946__dff.4 (Q), _0946__led.1 (I), _0994__mux1.3 (I0), _1007__mux1.3 (I0), _1008__mux1.1 (I1)
dest[9]: _0947__dff.4 (Q), _0947__led.1 (I), _0995__mux1.3 (I0), _1008__mux1.3 (I0), _1009__mux1.1 (I1)
dest[10]: _0839_.3 (I0), _0948__dff.4 (Q), _0948__led.1 (I), _1009__mux1.3 (I0), _1010__mux1.1 (I1)
dest[11]: _0875__and_gate.2 (A), _0949__dff.4 (Q), _0949__led.1 (I), _1010__mux1.3 (I0), _1011__mux1.1 (I1)
dest[12]: _0846_.1 (A), _0950__dff.4 (Q), _0950__led.1 (I), _1011__mux1.3 (I0), _1012__mux1.1 (I1)
dest[13]: _0951__dff.4 (Q), _0951__led.1 (I), _0996__mux1.3 (I0), _1012__mux1.3 (I0), _1013__mux1.1 (I1)
dest[14]: _0952__dff.4 (Q), _0952__led.1 (I), _0997__mux1.3 (I0), _1013__mux1.3 (I0), _1014__mux1.1 (I1)
dest[15]: _0953__dff.4 (Q), _0953__led.1 (I), _0964__mux1.1 (I1), _0998__mux1.3 (I0), _1014__mux1.3 (I0)
dest[16]: _0738_.1 (B), _0758_.2 (A), _0880__dff.4 (Q), _0880__led.1 (I)
dia[0]: _0786_.3 (I0), _0897__dff.4 (Q), _0897__led.1 (I), _0973__mux1.3 (I0)
dia[1]: _0788_.3 (I0), _0898__dff.4 (Q), _0898__led.1 (I), _0974__mux1.3 (I0)
dia[2]: _0789_.3 (I0), _0899__dff.4 (Q), _0899__led.1 (I), _0975__mux1.3 (I0)
dia[3]: _0790_.3 (I0), _0900__dff.4 (Q), _0900__led.1 (I), _0976__mux1.3 (I0)
dia[4]: _0791_.3 (I0), _0901__dff.4 (Q), _0901__led.1 (I), _0977__mux1.3 (I0)
dia[5]: _0792_.3 (I0), _0902__dff.4 (Q), _0902__led.1 (I), _0978__mux1.3 (I0)
dia[6]: _0793_.3 (I0), _0903__dff.4 (Q), _0903__led.1 (I), _0979__mux1.3 (I0)
dia[7]: _0712_.3 (I0), _0904__dff.4 (Q), _0904__led.1 (I), _0980__mux1.3 (I0)
dib[0]: _0774_.3 (I0), _0889__dff.4 (Q), _0889__led.1 (I), _0965__mux1.1 (I1)
dib[1]: _0775_.3 (I0), _0890__dff.4 (Q), _0890__led.1 (I), _0966__mux1.1 (I1)
dib[2]: _0776_.3 (I0), _0891__dff.4 (Q), _0891__led.1 (I), _0967__mux1.1 (I1)
dib[3]: _0777_.3 (I0), _0892__dff.4 (Q), _0892__led.1 (I), _0968__mux1.1 (I1)
dib[4]: _0778_.3 (I0), _0893__dff.4 (Q), _0893__led.1 (I), _0969__mux1.1 (I1)
dib[5]: _0779_.3 (I0), _0894__dff.4 (Q), _0894__led.1 (I), _0970__mux1.1 (I1)
dib[6]: _0780_.3 (I0), _0895__dff.4 (Q), _0895__led.1 (I), _0971__mux1.1 (I1)
dib[7]: _0711_.1 (A), _0896__dff.4 (Q), _0896__led.1 (I), _0972__mux1.1 (I1)
io_in[0]: _0636_.6 (C), _0648_.1 (B), _0685_.2 (A), _0694_.6 (C), _0958__dff.3 (D), pin8_io.1 (FROM_HEADER[0])
io_in[1]: _0636_.3 (B), _0648_.2 (A), _0686_.2 (A), _0694_.3 (B), _0707_.2 (A), _0959__dff.3 (D), _1023__mux1.3 (I0), pin8_io.2 (FROM_HEADER[1])
io_in[2]: _0636_.1 (A), _0649_.1 (B), _0660_.6 (C), _0698_.3 (B), _0960__dff.3 (D), pin8_io.3 (FROM_HEADER[2])
io_in[3]: _0642_.2 (A), _0649_.2 (A), _0961__dff.3 (D), pin8_io.4 (FROM_HEADER[3])
io_in[4]: _0674_.1 (B), _0713_.3 (B), fanout7.2 (A), pin8_io.5 (FROM_HEADER[4])
io_in[5]: _0674_.2 (A), _0713_.1 (A), fanout6.2 (A), pin8_io.6 (FROM_HEADER[5])
io_in[6]: _0712_.6 (S), _0715_.6 (S), fanout2.2 (A), pin8_io.7 (FROM_HEADER[6])
io_in[7]: _0667_.1 (A), _0669_.1 (A), _0710_.2 (A), _0711_.3 (B), _0724_.2 (A), _0739_.2 (A), _0769_.2 (A), pin8_io.8 (FROM_HEADER[7])
mar[0]: _0866__and_or.1 (A), _0867__and_gate.2 (A), _0914__dff.4 (Q), _0914__led.1 (I)
mar[1]: _0867__and_or.1 (A), _0868__and_gate.2 (A), _0915__dff.4 (Q), _0915__led.1 (I)
mar[2]: _0868__and_or.1 (A), _0869__and_gate.2 (A), _0916__dff.4 (Q), _0916__led.1 (I)
mar[3]: _0869__and_or.1 (A), _0870__and_gate.2 (A), _0917__dff.4 (Q), _0917__led.1 (I)
mar[4]: _0870__and_or.1 (A), _0871__and_gate.2 (A), _0918__dff.4 (Q), _0918__led.1 (I)
mar[5]: _0871__and_or.1 (A), _0872__and_gate.2 (A), _0919__dff.4 (Q), _0919__led.1 (I)
mar[6]: _0872__and_or.1 (A), _0873__and_gate.2 (A), _0920__dff.4 (Q), _0920__led.1 (I)
mar[7]: _0873__and_or.1 (A), _0921__dff.4 (Q), _0921__led.1 (I)
mc14500__IEN_l: _0726_.1 (A), _0877__dff.4 (Q), _0877__led.1 (I), _0877__mux.3 (I0)
mc14500__OEN_l: _0665_.3 (B), _0697_.2 (A), _0876__dff.4 (Q), _0876__led.1 (I), _0876__mux.3 (I0)
mc14500__instr_l[0]: _0635_.6 (C), _0687_.1 (B), _0692_.2 (A), _0705_.3 (B), _0728_.1 (B), _0798_.1 (A), _0958__dff.4 (Q), _0958__led.1 (I)
mc14500__instr_l[1]: _0635_.3 (B), _0662_.2 (A), _0701_.3 (I0), _0728_.2 (A), _0959__dff.4 (Q), _0959__led.1 (I)
mc14500__instr_l[2]: _0635_.1 (A), _0659_.2 (A), _0682_.1 (B), _0699_.1 (B), _0960__dff.4 (Q), _0960__led.1 (I)
mc14500__instr_l[3]: _0644_.1 (B), _0682_.2 (A), _0961__dff.4 (Q), _0961__led.1 (I)
mc14500__skip: _0641_.2 (A), _0661_.6 (C), _0684_.2 (A), _0695_.1 (A), _0742_.1 (A), _0956__dff.4 (Q), _0956__led.1 (I)
net1: _0664_.1 (B), _0690_.1 (B), _0735_.3 (B), _0744_.3 (B), _0760_.1 (B), _0797_.6 (C), _0815_.3 (B), _0821_.3 (B), fanout1.4 (Y)
net2: _0658_.2 (A), _0669_.3 (B), _0717_.6 (S), _0719_.6 (S), _0722_.6 (S), _0739_.1 (B), _0770_.3 (B), _0858_.3 (B), fanout2.4 (Y)
net3: _1003__mux1.6 (S), _1004__mux1.6 (S), _1005__mux1.6 (S), _1006__mux1.6 (S), _1007__mux1.6 (S), _1008__mux1.6 (S), _1009__mux1.6 (S), _1010__mux1.6 (S), _1011__mux1.6 (S), _1012__mux1.6 (S), max_cap3.4 (Y)
net4: _0820_.1 (B), _0839_.6 (S), _0843_.2 (A), _0991__mux1.6 (S), _0992__mux1.6 (S), _0994__mux1.6 (S), _0995__mux1.6 (S), _0996__mux1.6 (S), _0997__mux1.6 (S), _0998__mux1.6 (S), max_cap4.4 (Y)
net5: _0771_.1 (B), _0773_.1 (A), _0774_.6 (S), _0775_.6 (S), _0776_.6 (S), _0777_.6 (S), _0778_.6 (S), _0779_.6 (S), fanout5.4 (Y)
net6: _0668_.1 (A), _0670_.1 (A), _0672_.2 (A), _0676_.2 (A), _0716_.1 (A), _0723_.1 (A), _0781_.1 (A), _0783_.6 (C), fanout6.4 (Y)
net7: _0668_.3 (B), _0670_.3 (B), _0671_.2 (A), _0677_.1 (B), _0720_.2 (A), _0723_.3 (B), _0781_.3 (B), _0784_.1 (A), fanout7.4 (Y)
out_1: _0863_.3 (I0), _0955__dff.4 (Q), _0955__led.1 (I)
out_2: _0860_.3 (I0), _0954__dff.4 (Q), _0954__led.1 (I)
rst_latency[0]: _0663_.1 (B), _0764_.2 (A), _0767_.3 (B), _0887__dff.4 (Q), _0887__led.1 (I)
rst_latency[1]: _0663_.2 (A), _0766_.1 (A), _0767_.1 (A), _0888__dff.4 (Q), _0888__led.1 (I)
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
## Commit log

2024-06-23 Make this work in a docker image
2024-06-23 Use correct branch in dockerfile
2024-06-24 Add some examples.
2024-08-19 Update example
